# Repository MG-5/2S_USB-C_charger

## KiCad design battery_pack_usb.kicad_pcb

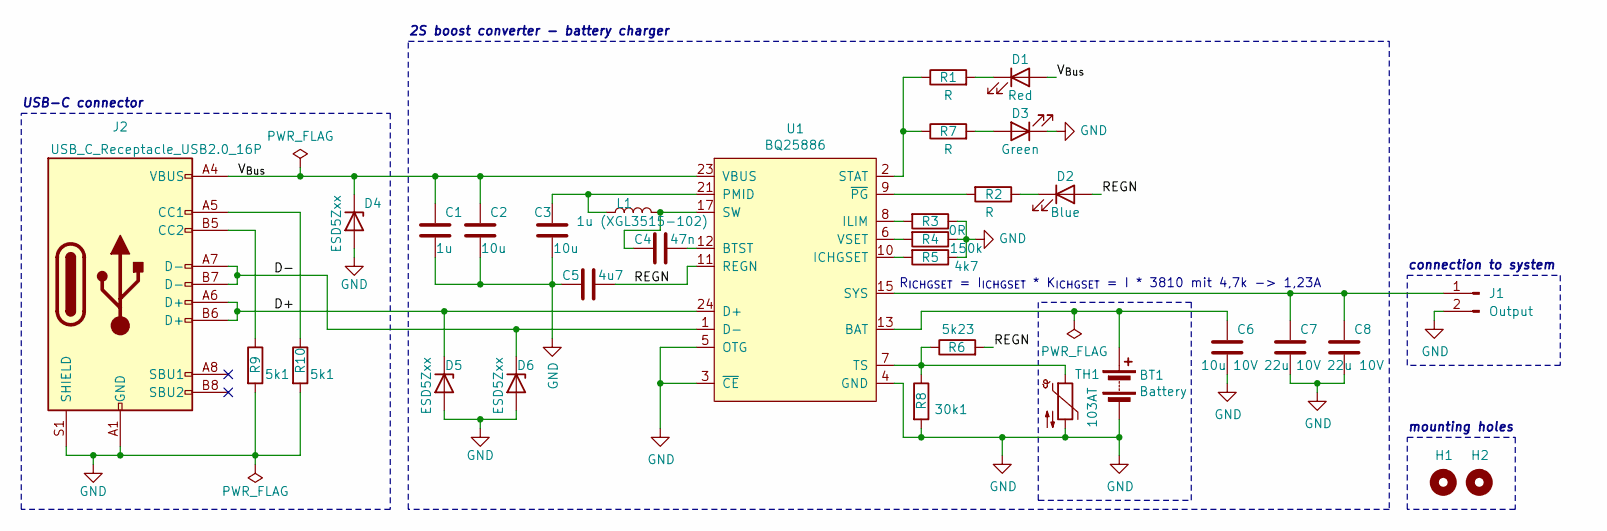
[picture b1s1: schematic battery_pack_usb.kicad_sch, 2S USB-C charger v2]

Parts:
BT1: Battery; Molex_PicoBlade_53047-0210_1x02_P1.25mm_Vertical
C1: 1u; C_0603_1608Metric_Pad1.08x0.95mm_HandSolder
C2, C3: 10u; C_0805_2012Metric_Pad1.18x1.45mm_HandSolder
C4: 47n; C_0603_1608Metric_Pad1.08x0.95mm_HandSolder
C5: 4u7; C_0603_1608Metric_Pad1.08x0.95mm_HandSolder
C6: 10u 10V; C_0805_2012Metric_Pad1.18x1.45mm_HandSolder
C7, C8: 22u 10V; C_0805_2012Metric_Pad1.18x1.45mm_HandSolder
D1: Red; Molex_PicoBlade_53047-0210_1x02_P1.25mm_Vertical
D2: Blue; LED_0603_1608Metric_Pad1.05x0.95mm_HandSolder
D3: Green; Molex_PicoBlade_53047-0210_1x02_P1.25mm_Vertical
D4, D5, D6: ESD5Zxx; D_SOD-523
H1, H2: MountingHole; MountingHole_3.2mm_M3_ISO14580
J1: Output; Molex_PicoBlade_53047-0210_1x02_P1.25mm_Vertical
J2: USB_C_Receptacle_USB2.0_16P; USB_C_Receptacle_Palconn_UTC16-G
L1: 1u (XGL3515-102); XxL3515
R1, R2, R7: R; R_0603_1608Metric_Pad0.98x0.95mm_HandSolder
R3: 0R; R_0603_1608Metric_Pad0.98x0.95mm_HandSolder
R4: 150k; R_0603_1608Metric_Pad0.98x0.95mm_HandSolder
R5: 4k7; R_0603_1608Metric_Pad0.98x0.95mm_HandSolder
R6: 5k23; R_0603_1608Metric_Pad0.98x0.95mm_HandSolder
R8: 30k1; R_0603_1608Metric_Pad0.98x0.95mm_HandSolder
R9, R10: 5k1; R_0603_1608Metric_Pad0.98x0.95mm_HandSolder
TH1: 103AT; Molex_PicoBlade_53047-0210_1x02_P1.25mm_Vertical
U1: BQ25886; VQFN-24-1EP_4x4mm_P0.5mm_EP2.45x2.45mm_ThermalVias

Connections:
/D+: D5.1 (K), J2.A6 (D+), J2.B6 (D+), U1.24 (D+)
/D-: D6.1 (K), J2.A7 (D-), J2.B7 (D-), U1.1 (D-)
/REGN: C5.1, D2.2 (A), R6.2, U1.11 (REGN)
/V_{Bus}: C1.1, C2.1, D1.2 (A), D4.1 (K), J2.A4 (VBUS), J2.A9 (VBUS), J2.B4 (VBUS), J2.B9 (VBUS), U1.23 (VBUS)
BAT: BT1.1 (+), C6.1, U1.13 (BAT), U1.14 (BAT)
GND: BT1.2 (-), C1.2, C2.2, C3.1, C5.2, C6.2, C7.2, C8.2, D3.1 (K), D4.2 (A), D5.2 (A), D6.2 (A), J1.2, J2.A1 (GND), J2.A12 (GND), J2.B1 (GND), J2.B12 (GND), J2.S1 (SHIELD), R3.1, R4.1, R5.1, R8.2, R9.2, R10.2, TH1.2, U1.3 (~CE), U1.4 (GND), U1.5 (OTG), U1.19 (GND), U1.20 (GND), U1.25 (GND)
unnamed: C3.2, L1.1, U1.21 (PMID), U1.22 (PMID)
unnamed: C4.2, L1.2, U1.17 (SW), U1.18 (SW)
unnamed: D1.1 (K), R1.2
unnamed: D2.1 (K), R2.1
unnamed: D3.2 (A), R7.2
unnamed: C7.1, C8.1, J1.1, U1.15 (SYS), U1.16 (SYS)
unnamed: J2.A5 (CC1), R10.1
unnamed: J2.B5 (CC2), R9.1
unnamed: C4.1, U1.12 (BTST)
unnamed: R5.2, U1.10 (ICHGSET)
unnamed: R3.2, U1.8 (ILIM)
unnamed: R1.1, R7.1, U1.2 (STAT)
unnamed: R6.1, R8.1, TH1.1, U1.7 (TS)
unnamed: R4.2, U1.6 (VSET)
unnamed: R2.2, U1.9 (~PG)

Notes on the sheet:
USB-C connector
mounting holes
2S boost converter - battery charger
connection to system
R_{ICHGSET} = I_{ICHGSET} * K_{ICHGSET} = I * 3810 mit 4,7k -> 1,23A

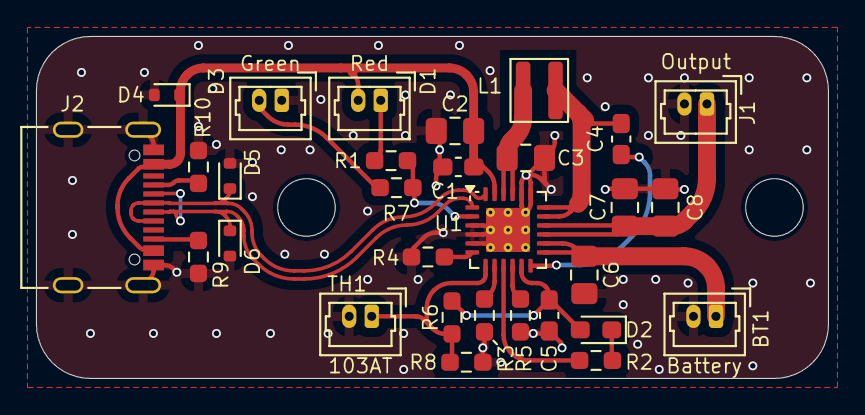
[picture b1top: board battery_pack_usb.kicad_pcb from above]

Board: 2 copper layers, 44.0 x 19.0 mm, 32 parts (0 on the bottom side), 21 nets.

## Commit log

2020-08-07 Init
2020-08-07 Finish schematic
2020-08-12 Annotate and assign
2020-08-15 Finish PCB
2020-09-05 Add voltages to capacitances
2023-10-21 Add license
2023-10-21 Convert to KiCad 7.0.8
2023-10-22 Add note to USB-C power delivery
2024-06-13 Improve circuit and PCB
